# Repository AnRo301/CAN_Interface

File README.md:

# CAN Interface for ESP32

## Introduction

ESP32-Development-Boards contain powerful and inexpensive 32-bit microcontrollers and are well known for their low energy consumption. Due to their open design, the modules are well suited for (IoT) Internet of Things applications

CAN is a popular communication protocol in the automotive sector. It is a reliable and robust protocol which is designed for high-speed data transmission and real-time applications.
Although the microcontrollers have both CAN and Ethernet controllers integrated, there are currently no inexpensive boards available that provide an interface for the CAN bus.

Within this project, a circuit board is developed, which provides an interface between an ESP32 board and the CAN bus.

## Features

- Send and receive CAN Messages according to ISO11898-1
- Standard and extended frame format supported
- Various bus speeds supported
- Acts as a WLAN access point
- Received CAN messages are forwarded via web socket and can be viewed via a web interface on any device that is connected to the provided network
- Messages that are to be sent via the bus can be entered using the web interface and are transmitted via web socket to the microcontroller, which initiates the sending via CAN Bus

## Third Party Components
Hardware:
- esp32-s3-devkit-1
- USB-C cables
- SubD cable or twisted pair of jumper cables
- any device that supports wifi (computer/ tablet/ phone)

Software:
- Visual Studio Code
- Required Extension Packages:
  - PlatformIO IDE
  - Arduino
  - ESP-IDF
  
## How to run the project?
- Connect CAN Bus module to ESP32-S3 (pin labels must match)

- Connect to the CAN Bus either via SubD cable or via twisted pair of jumper cables (Pin Header: H (CAN High), L (CAN Low))
- Depending on the type of connection to the CAN bus (Subd or jumper cables) connect the pin headers via jumpers according to the following picture
  (A terminating resistor of 120 ohms is added between CAN High and CAN Low via JP1)

- Install extension packages mentioned in 'Third Party Components' in VS Code
- Connect ESP32-S3 via USB-C Port to the pc
- Build and Upload Filesystem Image with PlatformIO
- Connect ESP32-S3 via USB-C COM Port to the pc
- Build and upload the Code with PlatformIO

- Connect any device to the Wifi "CAN2WLAN" provided by the ESP32 acting as an access point
- Type in the following IP-Adresse in a browser: 192.168.4.1
- The following user interface should now appear:

Warning: Messages needs to be typed in in the right format. No detection of wrong/ unplausible input is implemented !

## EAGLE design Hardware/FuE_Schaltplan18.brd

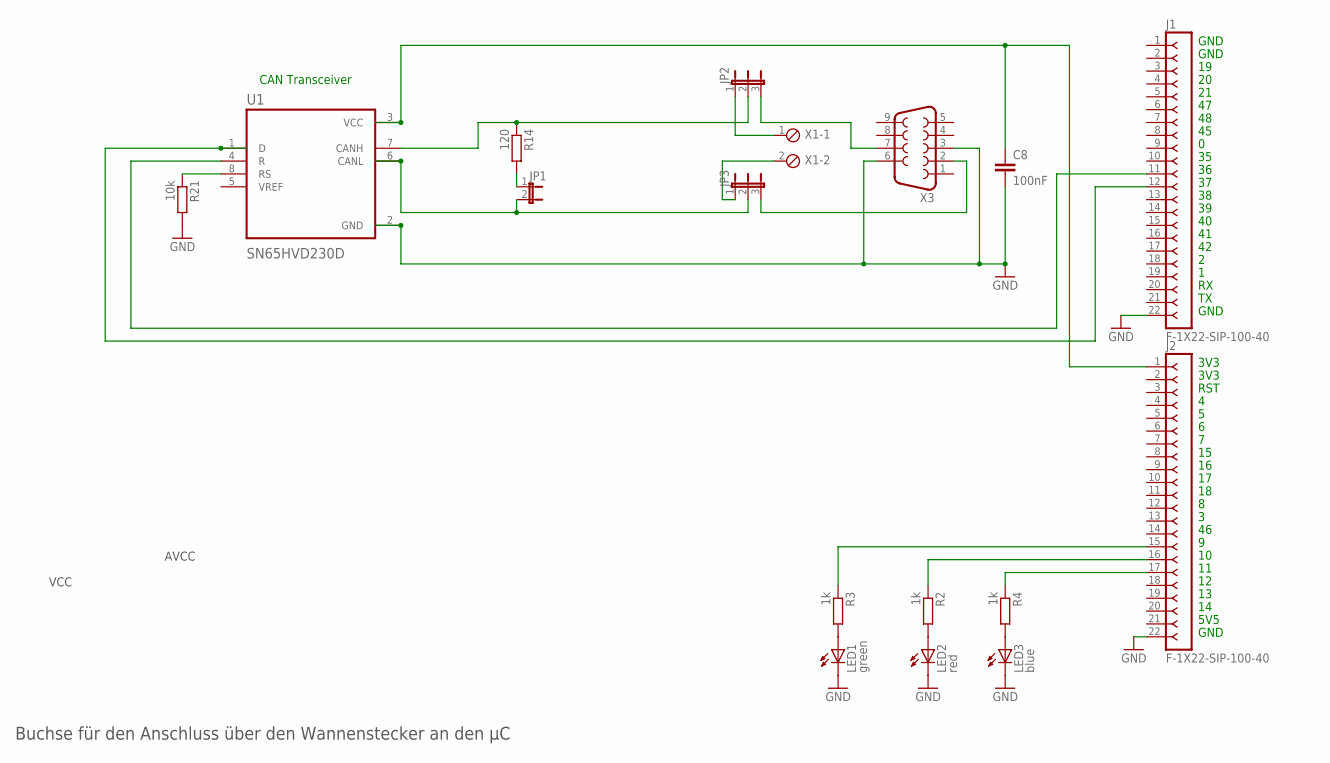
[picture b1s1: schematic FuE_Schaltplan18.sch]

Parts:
C8: 100nF; C0805
J1, J2: F-1X22-SIP-100-40; SIP-100-22-40
JP1: JP1E; JP1
JP2, JP3: JP2E; JP2
LED1: green; CHIP-LED0805
LED2: red; CHIP-LED0805
LED3: blue; CHIP-LED0805
R2, R3, R4: 1k; R0805
R14: 120; R0805
R21: 10k; R0805
U1: SN65HVD230D; SOIC127P599X175-8N
X1: MPT2; 2POL254
X3: F09VP

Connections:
GND: C8.2, J1.22, J2.22, LED1.C, LED2.C, LED3.C, R21.2, U1.2 (GND), X3.3, X3.6
unnamed: C8.1, J2.1, U1.3 (VCC)
unnamed: J1.11, U1.4 (R)
unnamed: LED2.A, R2.2
unnamed: R21.1, U1.8 (RS)
unnamed: JP1.2, JP3.2, U1.6 (CANL)
unnamed: J2.16, R2.1
unnamed: LED1.A, R3.2
unnamed: LED3.A, R4.2
unnamed: J2.15, R3.1
unnamed: J2.17, R4.1
unnamed: JP2.3, X3.7
unnamed: JP2.2, R14.1, U1.7 (CANH)
unnamed: J1.12, U1.1 (D)
unnamed: JP3.3, X3.2
unnamed: JP1.1, R14.2
unnamed: JP2.1, X1.1
unnamed: JP3.1, X1.2

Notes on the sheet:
AVCC
VCC
Buchse für den Anschluss über den Wannenstecker an den µC
CAN Transceiver
GND
3V3
RST
5V5

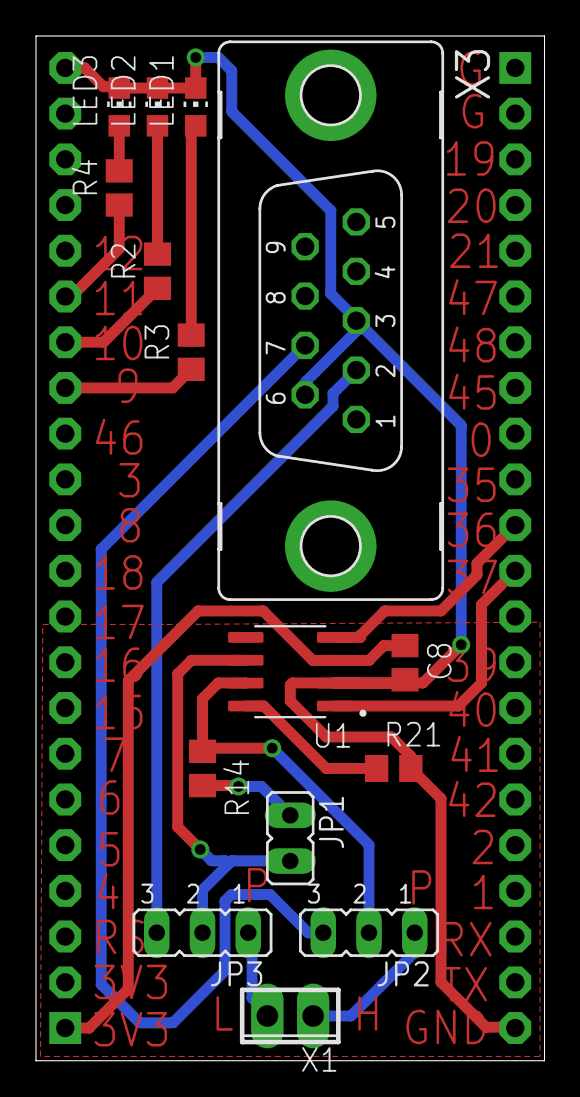
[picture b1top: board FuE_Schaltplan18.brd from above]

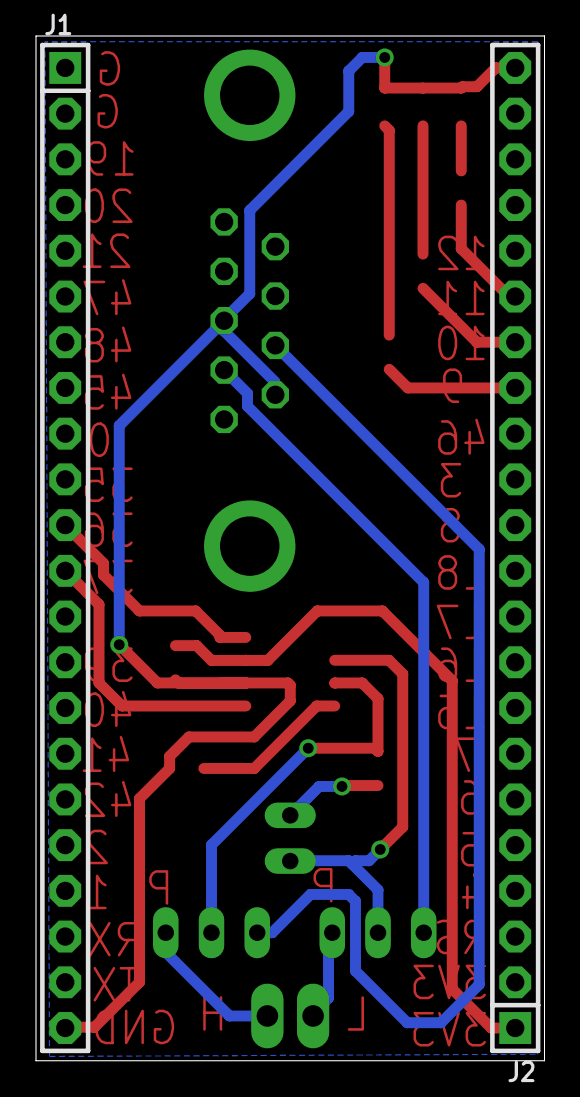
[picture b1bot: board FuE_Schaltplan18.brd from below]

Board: 2 copper layers, 28.2 x 56.9 mm, 17 parts (2 on the bottom side), 18 nets.

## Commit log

2024-03-19 modified: ESP32/src/main.cpp
2024-03-21 modified: ESP32/include/Access_Point.h
2024-03-22 modified: ESP32/data/index.html modified: ESP32/data/script.js modified: ESP32/data/style.css modified: ESP32/include/CAN.h modified: ESP32/src/Access_Point.cpp modified: ESP32/src/CAN.cpp
2024-03-23 modified: ESP32/src/Access_Point.cpp modified: ESP32/src/CAN.cpp
2024-03-24 modified: ESP32/data/index.html modified: ESP32/data/script.js modified: ESP32/include/Access_Point.h modified: ESP32/include/CAN.h modified: ESP32/src/Access_Point.cpp modified: ESP32/src/CAN.cpp
2024-03-25 modified: ESP32/data/script.js

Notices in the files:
parts and their libraries:
con-headers-jp: Copyright (C) 2008, Bob Starr
